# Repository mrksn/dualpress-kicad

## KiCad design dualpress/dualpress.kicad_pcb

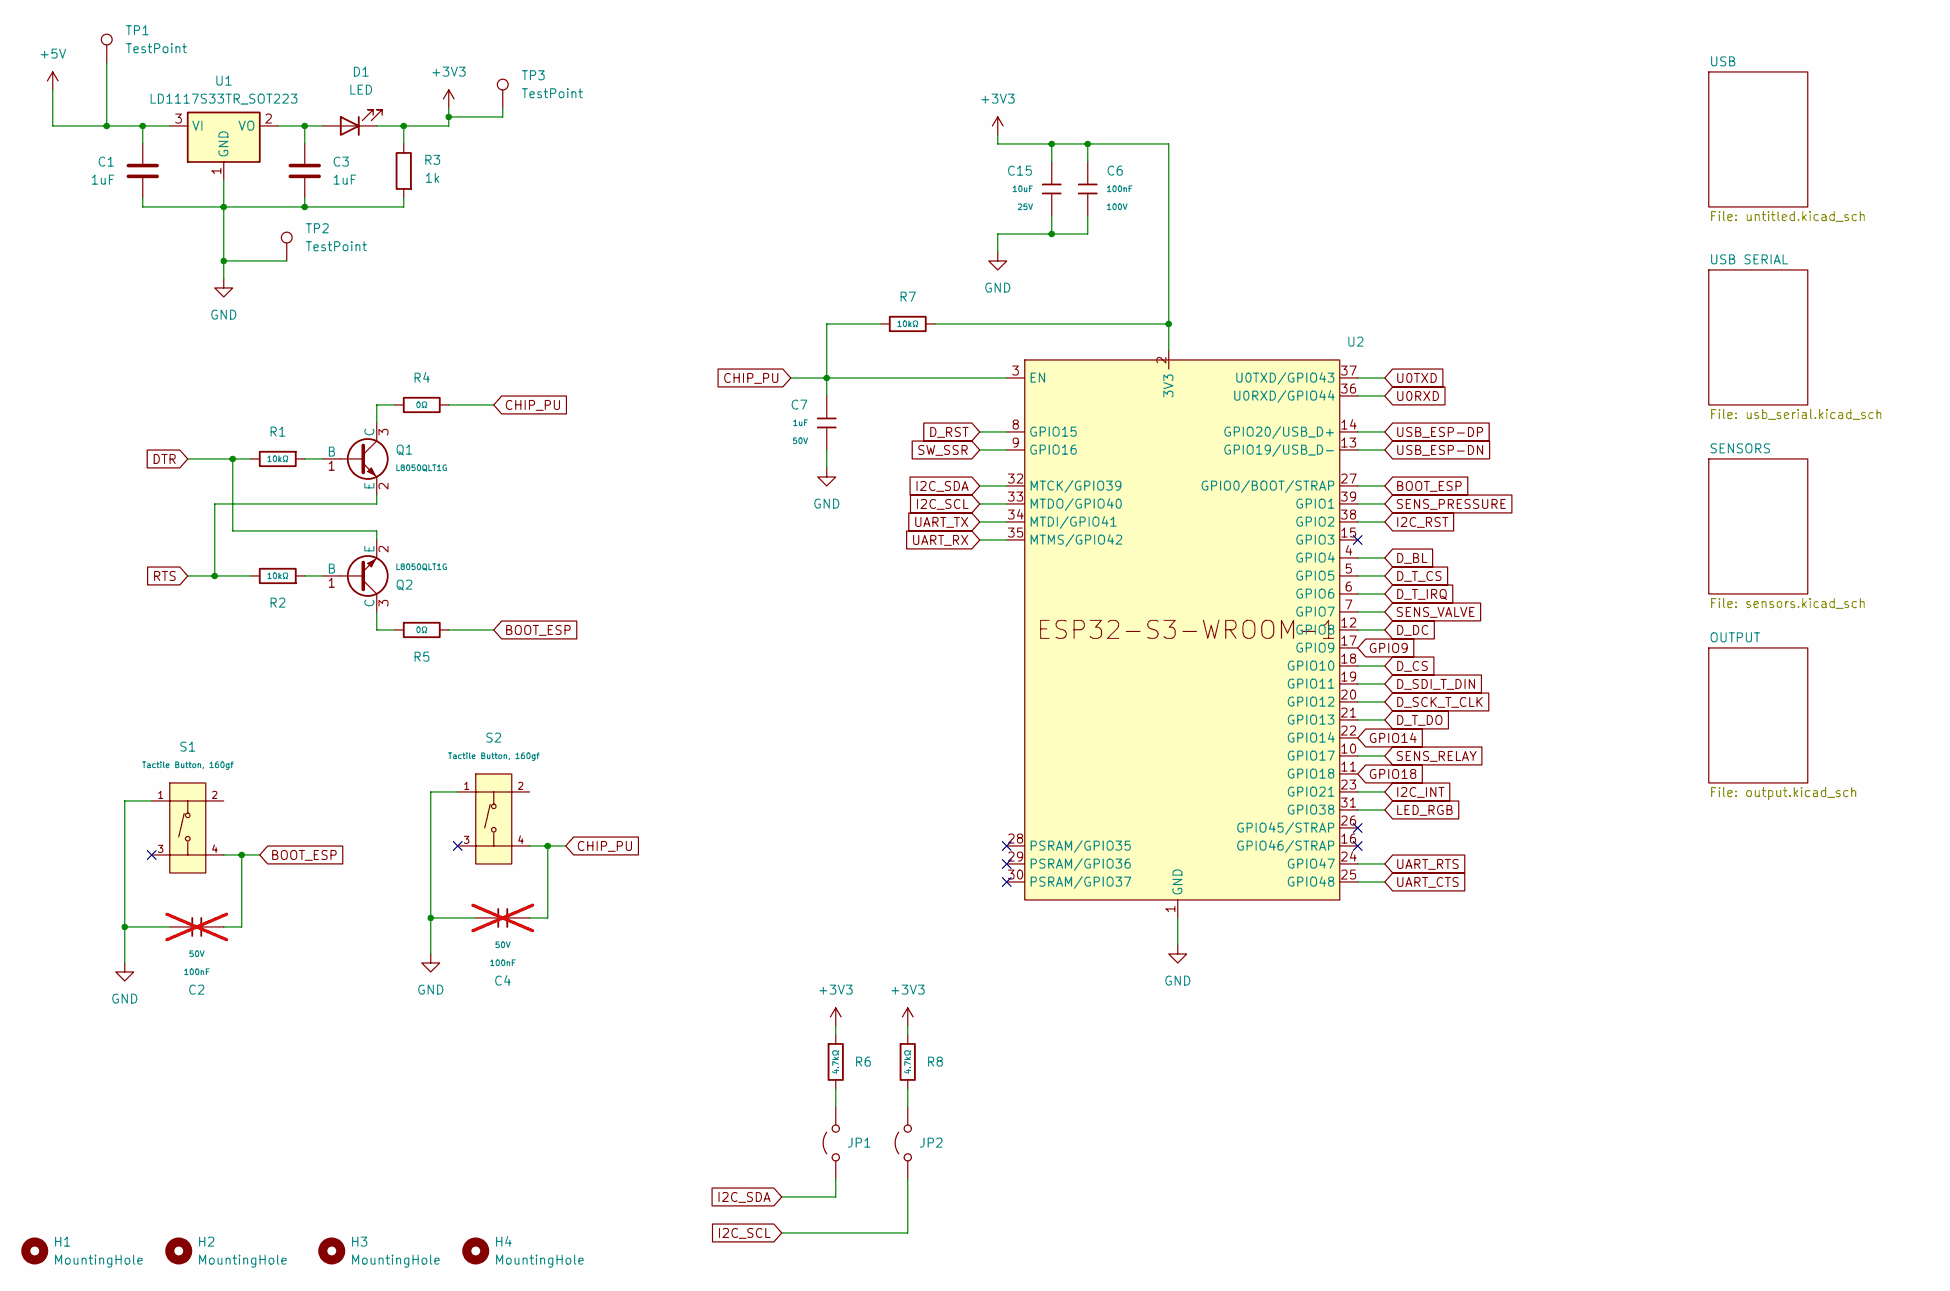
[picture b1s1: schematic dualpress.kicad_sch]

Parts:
C1, C3: 1uF; C_0805; JLCPCB C28323
C2, C4: 100nF; C_0805; Voltage Rated 50V; Tolerance ±10%; Part CC0603KRX7R9BB104; LCSC C14663; not fitted
C6: 100nF; C_0805; Voltage Rated 100V; Tolerance ±10%; Part CL21B104KCFNNNE; LCSC C28233
C7: 1uF; C_0805; Voltage Rated 50V; Tolerance ±10%; Part CL21B105KBFNNNE; LCSC C28323
C15: 10uF; C_0805; Voltage Rated 25V; Tolerance ±10%; Part CL21A106KAYNNNE; LCSC C15850
D1: LED; D_0603; JLCPCB C2286
H1, H2, H3, H4: MountingHole; MountingHole_3.2mm_M3
JP1, JP2: Jumper_2_Open; PinHeader_1x02_P2.54mm_Vertical
Q1: L8050QLT1G; Q_SOT-23; Part L8050QLT1G; LCSC C49581
Q2: L8050QLT1G; Q_SOT-23; Part SS8050; LCSC C7420370
R1, R2, R7: 10kΩ; R_0603; Overload Voltage (Max) 75V; Tolerance ±1%; Part 0603WAF1002T5E; LCSC C25804
R3: 1k; R_0603; JLCPCB C22548
R4, R5: 0Ω; R_0603; Overload Voltage (Max) 75V; Tolerance ±1%; Part 0603WAF0000T5E; LCSC C21189
R6, R8: 4.7kΩ; R_0603; Overload Voltage (Max) 75V; Tolerance ±1%; Part 0603WAF4701T5E; LCSC C23162
S1: Tactile Button, 160gf; Voltage Rating (Dc) 12V; Part TS-1088-AR02016; LCSC C720477
S2: Tactile Button, 160gf; Voltage Rating (Dc) 12V; Part TS-1187A-B-A-B; LCSC C318884
TP1, TP2, TP3: TestPoint; TestPoint_Pad_D1.5mm
U1: LD1117S33TR_SOT223; SOT-223-3_TabPin2; JLCPCB C86781
U2: ESP32-S3-WROOM-1; JLCPCB C2913202

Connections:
+3V3: C6.1, C15.1, D1.1 (K), R3.1, R6.1, R7.2, R8.1, TP3.1 (1_1), U2.2 (3V3); also elsewhere on the board
+5V: C1.2, TP1.1 (1_1), U1.3 (VI); also elsewhere on the board
BOOT_ESP: C2.1, R5.2, S1.4 (D), U2.27 (GPIO0/BOOT/STRAP)
CHIP_PU: C4.1, C7.1, R4.2, R7.1, S2.4 (D), U2.3 (EN)
DTR: Q2.2 (E), R1.2; also elsewhere on the board
D_BL: U2.4 (GPIO4); also elsewhere on the board
D_CS: U2.18 (GPIO10); also elsewhere on the board
D_DC: U2.12 (GPIO8); also elsewhere on the board
D_RST: U2.8 (GPIO15); also elsewhere on the board
D_SCK_T_CLK: U2.20 (GPIO12); also elsewhere on the board
D_SDI_T_DIN: U2.19 (GPIO11); also elsewhere on the board
D_T_CS: U2.5 (GPIO5); also elsewhere on the board
D_T_DO: U2.21 (GPIO13); also elsewhere on the board
D_T_IRQ: U2.6 (GPIO6); also elsewhere on the board
GND: C1.1, C2.2, C3.2, C4.2, C6.2, C7.2, C15.2, R3.2, S1.1 (A), S2.1 (A), TP2.1 (1_1), U1.1 (GND), U2.1 (GND); also elsewhere on the board
GPIO9: U2.17 (GPIO9); also elsewhere on the board
GPIO14: U2.22 (GPIO14); also elsewhere on the board
GPIO18: U2.11 (GPIO18); also elsewhere on the board
I2C_INT: U2.23 (GPIO21); also elsewhere on the board
I2C_RST: U2.38 (GPIO2); also elsewhere on the board
I2C_SCL: JP2.1 (A), U2.33 (MTDO/GPIO40); also elsewhere on the board
I2C_SDA: JP1.1 (A), U2.32 (MTCK/GPIO39); also elsewhere on the board
LED_RGB: U2.31 (GPIO38); also elsewhere on the board
unnamed: C3.1, D1.2 (A), U1.2 (VO)
unnamed: JP1.2 (B), R6.2
unnamed: JP2.2 (B), R8.2
unnamed: Q1.1 (B), R1.1
unnamed: Q1.3 (C), R4.1
unnamed: Q2.1 (B), R2.1
unnamed: Q2.3 (C), R5.1
unnamed: U2.40 (GND), U2.41 (GND)
RTS: Q1.2 (E), R2.2; also elsewhere on the board
SENS_PRESSURE: U2.39 (GPIO1); also elsewhere on the board
SENS_RELAY: U2.10 (GPIO17); also elsewhere on the board
SENS_VALVE: U2.7 (GPIO7); also elsewhere on the board
SW_SSR: U2.9 (GPIO16); also elsewhere on the board
U0RXD: U2.36 (U0RXD/GPIO44); also elsewhere on the board
U0TXD: U2.37 (U0TXD/GPIO43); also elsewhere on the board
UART_CTS: U2.25 (GPIO48); also elsewhere on the board
UART_RTS: U2.24 (GPIO47); also elsewhere on the board
UART_RX: U2.35 (MTMS/GPIO42); also elsewhere on the board
UART_TX: U2.34 (MTDI/GPIO41); also elsewhere on the board
USB_ESP-DN: U2.13 (GPIO19/USB_D-); also elsewhere on the board
USB_ESP-DP: U2.14 (GPIO20/USB_D+); also elsewhere on the board

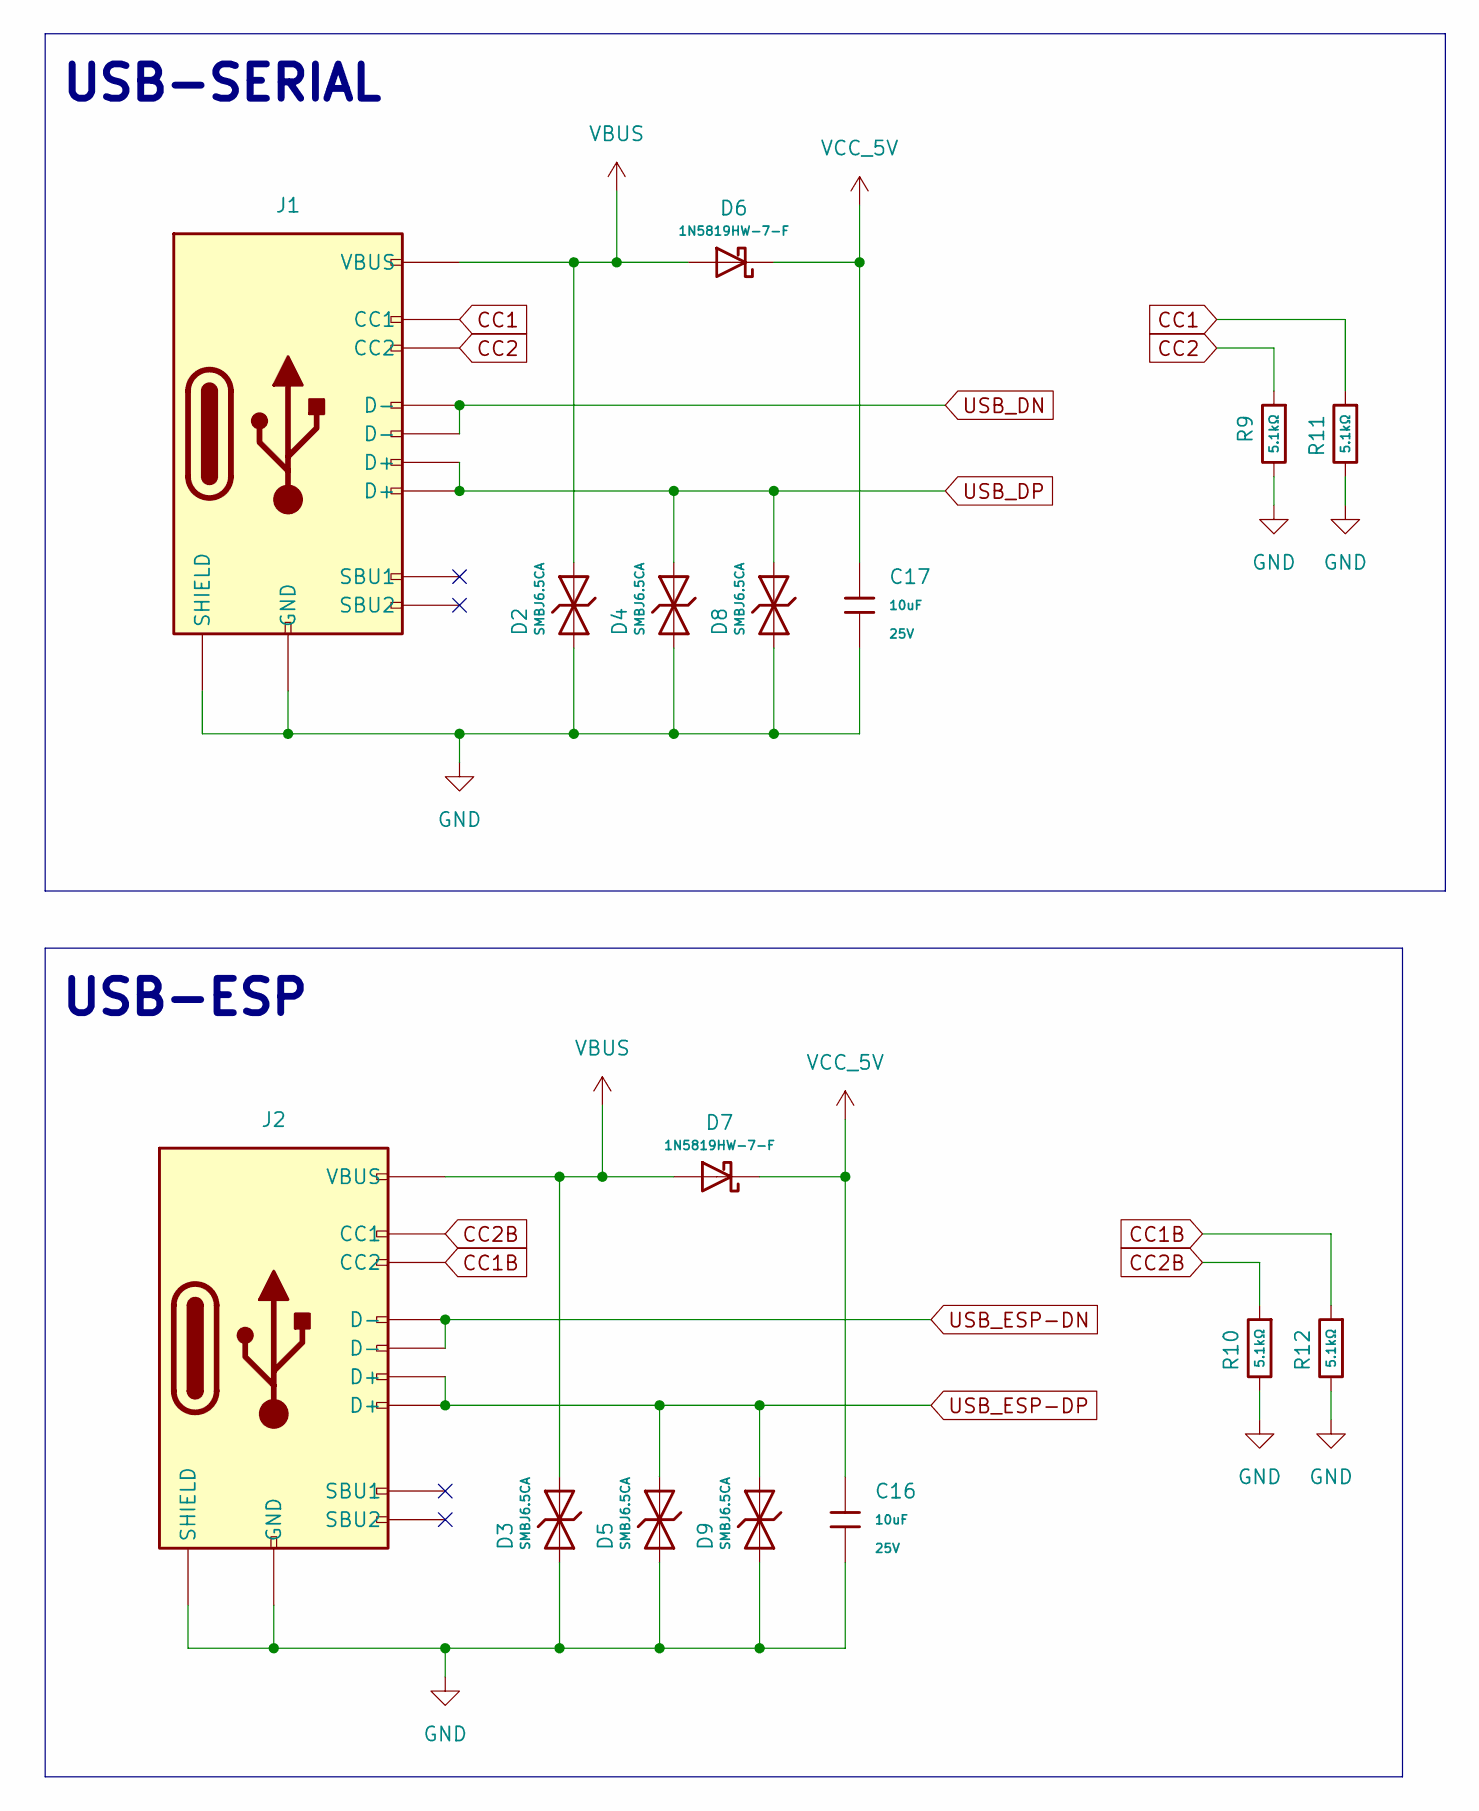
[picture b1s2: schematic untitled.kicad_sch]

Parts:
C16, C17: 10uF; C_0805; Voltage Rated 25V; Tolerance ±10%; Part CL21A106KAYNNNE; LCSC C15850
D2, D3, D4, D5, D8, D9: SMBJ6.5CA; D_SMB; Breakdown Voltage 7.22V; Part SMBJ6.5CA; LCSC C7420377
D6: 1N5819HW-7-F; D_SOD-123; Forward Voltage (Vf@If) 600mV@1A; Reverse Voltage (Vr) 40V; Part 1N5819HW-7-F; LCSC C82544
D7: 1N5819HW-7-F; D_SOD-123; Forward Voltage (Vf@If) 600mV@1A; Reverse Voltage (Vr) 40V; Part 1N5819WS; LCSC C191023
J1, J2: Connector, USB-TYPE-C-16P; TYPE-C-SMD_HX-TYPE-C-16PIN; LCSC C2927039
R9, R10, R11, R12: 5.1kΩ; R_0603; Overload Voltage (Max) 75V; Tolerance ±1%; Part 0603WAF5101T5E; LCSC C23186

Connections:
CC1: J1.A5 (CC1), R11.1
CC1B: J2.B5 (CC2), R12.1
CC2: J1.B5 (CC2), R9.1
CC2B: J2.A5 (CC1), R10.1
GND: C16.2, C17.2, D2.1, D3.1, D4.1, D5.1, D8.1, D9.1, J1.A12B1 (GND), J1.B12A1 (GND), J1.S1 (SHIELD), J2.A12B1 (GND), J2.B12A1 (GND), J2.S1 (SHIELD), R9.2, R10.2, R11.2, R12.2; also elsewhere on the board
USB_DN: J1.A7 (D-), J1.B7 (D-); also elsewhere on the board
USB_DP: D4.2, D8.2, J1.A6 (D+), J1.B6 (D+); also elsewhere on the board
USB_ESP-DN: J2.A7 (D-), J2.B7 (D-); also elsewhere on the board
USB_ESP-DP: D5.2, D9.2, J2.A6 (D+), J2.B6 (D+); also elsewhere on the board
VBUS: D2.2, D3.2, D6.2, D7.2, J1.A9B4 (VBUS), J1.B9A4 (VBUS), J2.A9B4 (VBUS), J2.B9A4 (VBUS); also elsewhere on the board
VCC_5V: C16.1, C17.1, D6.1, D7.1

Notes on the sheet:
USB-ESP
USB-SERIAL

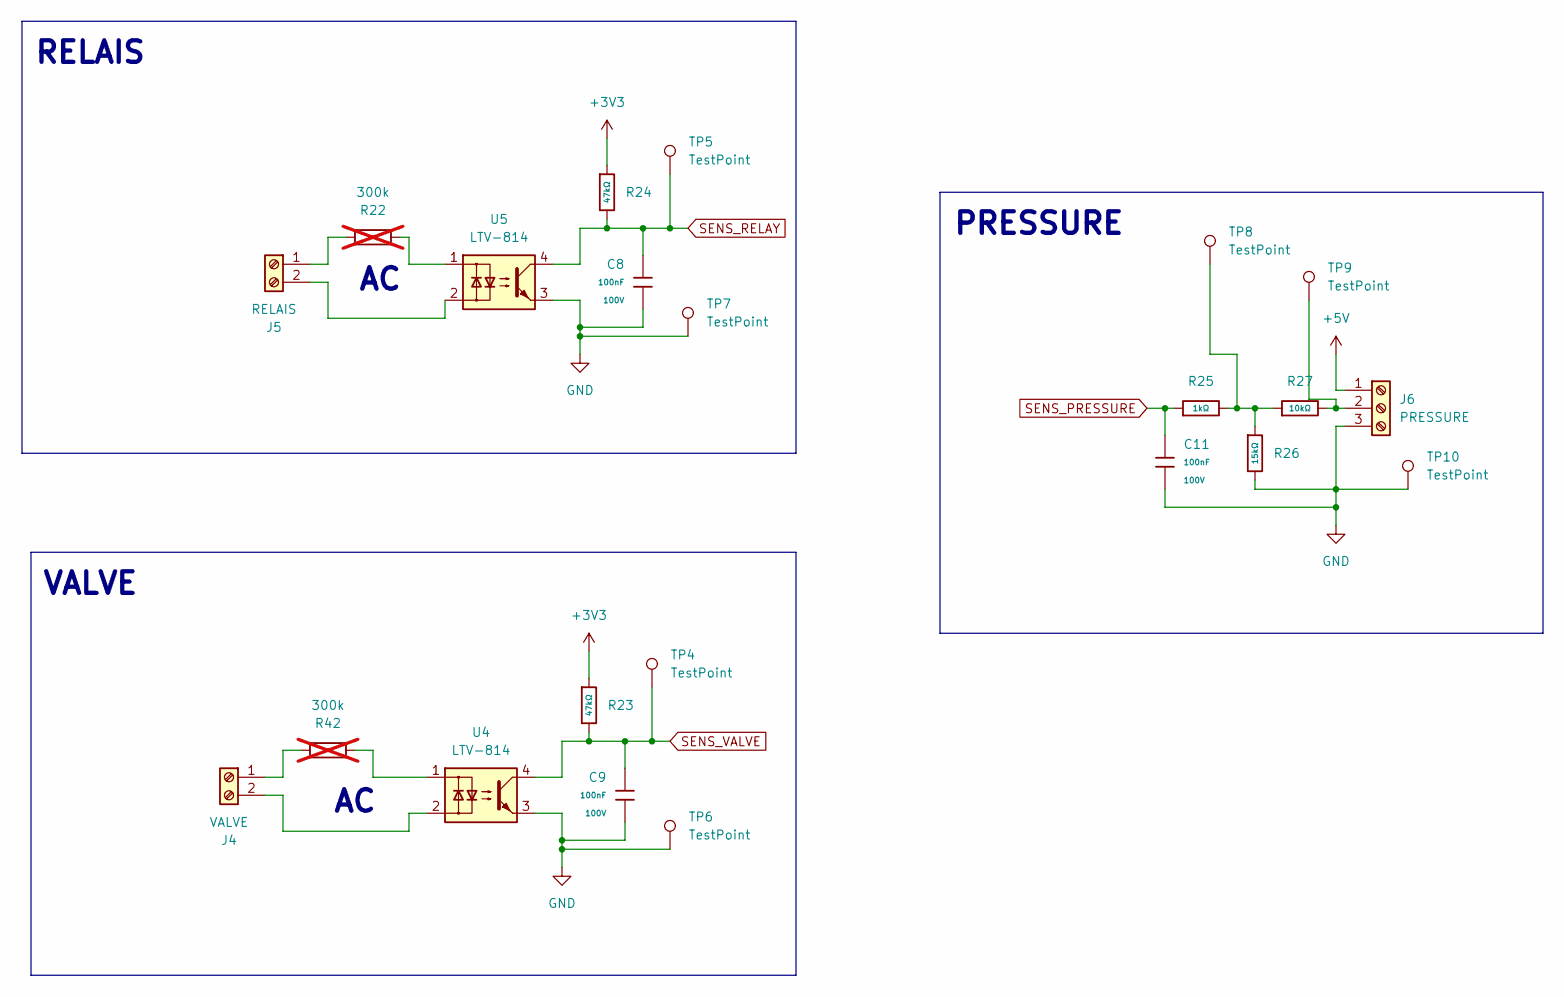
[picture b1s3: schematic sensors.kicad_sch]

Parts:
C8, C9, C11: 100nF; C_0805; Voltage Rated 100V; Tolerance ±10%; Part CL21B104KCFNNNE; LCSC C28233
J4: VALVE; TerminalBlock_MaiXu_MX126-5.0-02P_1x02_P5.00mm
J5: RELAIS; TerminalBlock_MaiXu_MX126-5.0-02P_1x02_P5.00mm
J6: PRESSURE; TerminalBlock_MaiXu_MX126-5.0-03P_1x03_P5.00mm
R22, R42: 300k; CP_Axial_L11.0mm_D5.0mm_P18.00mm_Horizontal; JLCPCB C601006; not fitted
R23, R24: 47kΩ; R_0603; Overload Voltage (Max) 75V; Tolerance ±1%; Part 0603WAF4702T5E; LCSC C25819
R25: 1kΩ; R_0603; Overload Voltage (Max) 75V; Tolerance ±1%; Part 0603WAF1001T5E; LCSC C21190
R26: 15kΩ; R_0603; Overload Voltage (Max) 75V; Tolerance ±1%; Part 0603WAF1502T5E; LCSC C22809
R27: 10kΩ; R_0603; Overload Voltage (Max) 75V; Tolerance ±1%; Part 0603WAF1002T5E; LCSC C25804
TP4, TP5, TP6, TP7, TP8, TP9, TP10: TestPoint; TestPoint_Pad_D1.5mm
U4, U5: LTV-814; DIP-4_W7.62mm; JLC C125118

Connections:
+3V3: R23.1, R24.1; also elsewhere on the board
+5V: J6.1; also elsewhere on the board
GND: C8.2, C9.2, C11.2, J6.3, R26.2, TP6.1 (1_1), TP7.1 (1_1), TP10.1 (1_1), U4.3, U5.3; also elsewhere on the board
unnamed: J4.1, R42.2
unnamed: J4.2, U4.2
unnamed: J5.1, R22.2
unnamed: J5.2, U5.2
unnamed: J6.2, R27.2, TP9.1 (1_1)
unnamed: R22.1, U5.1
unnamed: R25.2, R26.1, R27.1, TP8.1 (1_1)
unnamed: R42.1, U4.1
SENS_PRESSURE: C11.1, R25.1; also elsewhere on the board
SENS_RELAY: C8.1, R24.2, TP5.1 (1_1), U5.4; also elsewhere on the board
SENS_VALVE: C9.1, R23.2, TP4.1 (1_1), U4.4; also elsewhere on the board

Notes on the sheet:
PRESSURE
VALVE
RELAIS

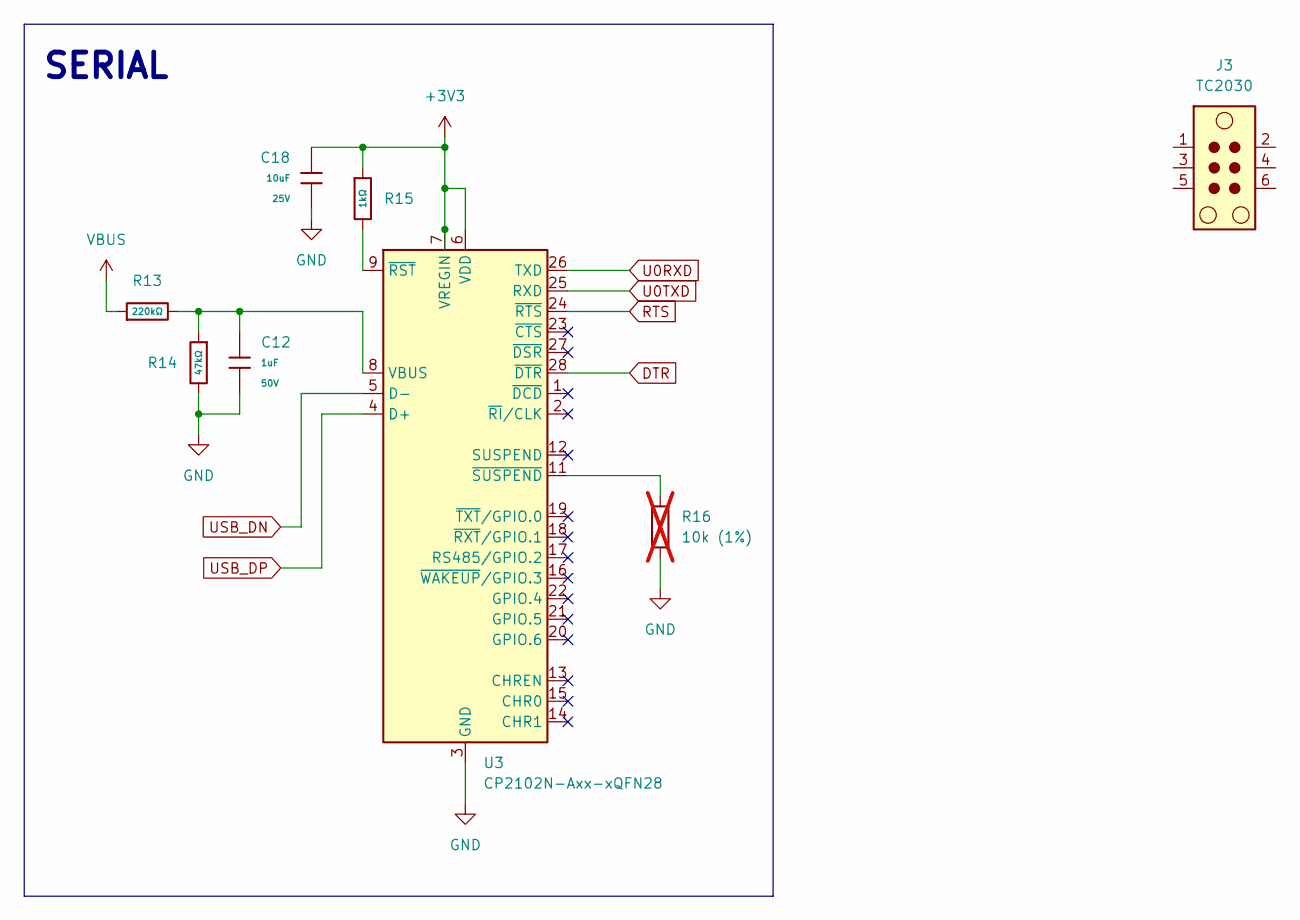
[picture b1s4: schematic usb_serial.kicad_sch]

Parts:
C12: 1uF; C_0805; Voltage Rated 50V; Tolerance ±10%; Part CL21B105KBFNNNE; LCSC C28323
C18: 10uF; C_0805; Voltage Rated 25V; Tolerance ±10%; Part CL21A106KAYNNNE; LCSC C15850
J3: TC2030; Tag-Connect_TC2030-IDC-NL_2x03_P1.27mm_Vertical
R13: 220kΩ; R_0603; Overload Voltage (Max) 75V; Tolerance ±1%; Part 0603WAF2203T5E; LCSC C22961
R14: 47kΩ; R_0603; Overload Voltage (Max) 75V; Tolerance ±1%; Part 0603WAF4702T5E; LCSC C25819
R15: 1kΩ; R_0603; Overload Voltage (Max) 75V; Tolerance ±1%; Part 0603WAF1001T5E; LCSC C21190
R16: 10k (1%); R_0603; JLCPCB C116677; not fitted
U3: CP2102N-Axx-xQFN28; QFN-28-1EP_5x5mm_P0.5mm_EP3.35x3.35mm; JLCPCB C964632

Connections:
+3V3: C18.1, R15.1, U3.6 (VDD), U3.7 (VREGIN); also elsewhere on the board
DTR: U3.28 (~DTR); also elsewhere on the board
GND: C12.2, C18.2, R14.2, R16.2, U3.3 (GND), U3.29 (GND); also elsewhere on the board
unnamed: C12.1, R13.2, R14.1, U3.8 (VBUS)
unnamed: R15.2, U3.9 (~RST)
unnamed: R16.1, U3.11 (~SUSPEND)
RTS: U3.24 (~RTS); also elsewhere on the board
U0RXD: U3.26 (TXD); also elsewhere on the board
U0TXD: U3.25 (RXD); also elsewhere on the board
USB_DN: U3.5 (D-); also elsewhere on the board
USB_DP: U3.4 (D+); also elsewhere on the board
VBUS: R13.1; also elsewhere on the board

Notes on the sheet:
SERIAL

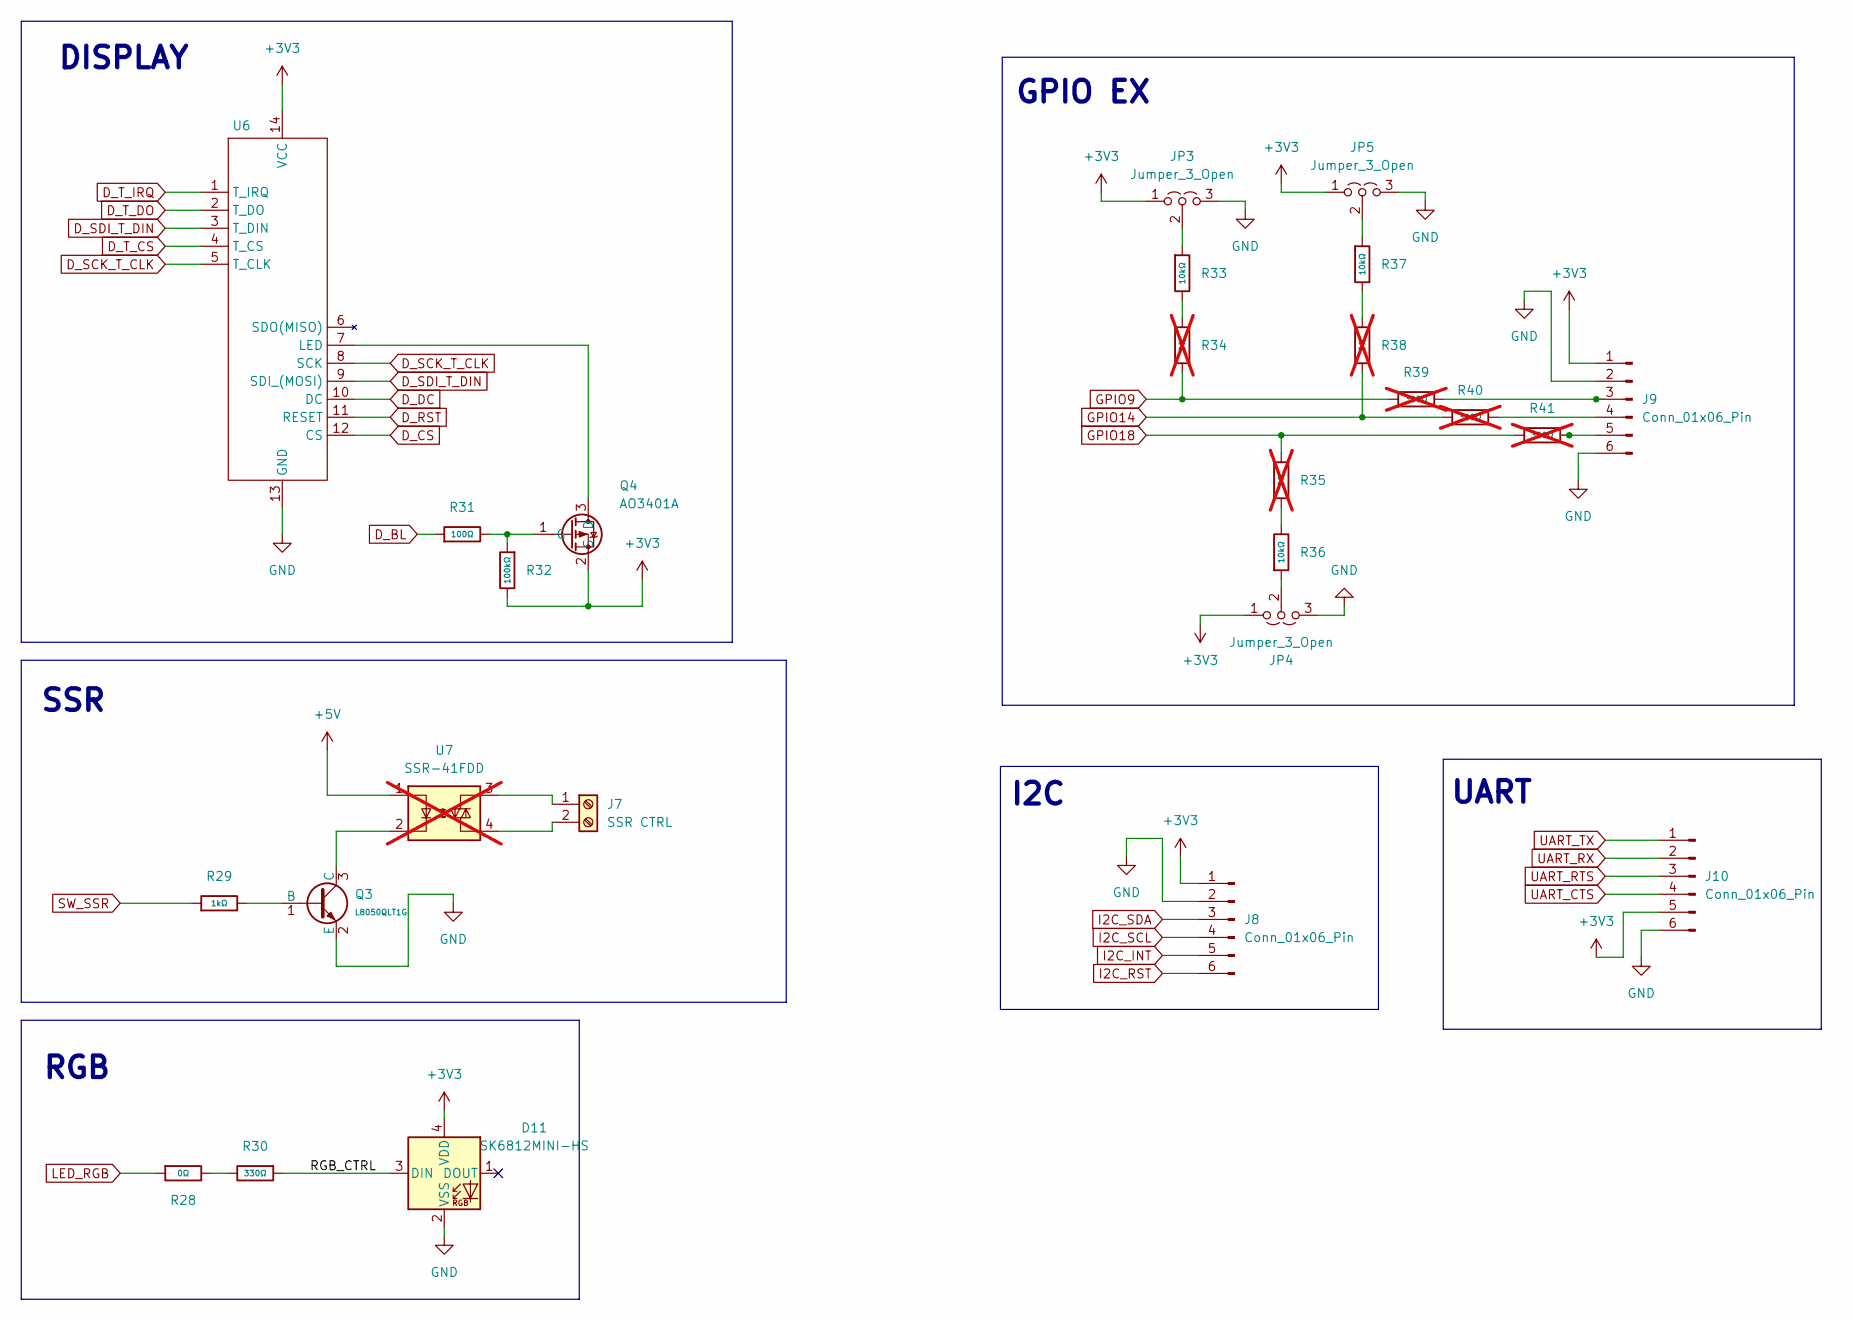
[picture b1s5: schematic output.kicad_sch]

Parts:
D11: SK6812MINI-HS; JLCPCB C2922787
J7: SSR CTRL; TerminalBlock_MaiXu_MX126-5.0-02P_1x02_P5.00mm
J8, J9, J10: Conn_01x06_Pin; JST_XH_B6B-XH-AM_1x06_P2.50mm_Vertical
JP3, JP4, JP5: Jumper_3_Open; PinHeader_1x03_P2.54mm_Vertical
Q3: L8050QLT1G; Q_SOT-23; Part S8050; LCSC C364312
Q4: AO3401A; SOT-23; JLCPCB C15127
R28: 0Ω; R_0603; Overload Voltage (Max) 75V; Tolerance ±1%; Part 0603WAF0000T5E; LCSC C21189
R29: 1kΩ; R_0603; Overload Voltage (Max) 75V; Tolerance ±1%; Part 0603WAF1001T5E; LCSC C21190
R30: 330Ω; R_0603; Overload Voltage (Max) 75V; Tolerance ±1%; Part 0603WAF3300T5E; LCSC C23138
R31: 100Ω; R_0805; Overload Voltage (Max) 150V; Tolerance ±1%; Part 0805W8F1000T5E; LCSC C17408
R32: 100kΩ; R_0603; Overload Voltage (Max) 150V; Tolerance ±1%; Part 0805W8F1003T5E; LCSC C149504
R33, R36, R37: 10kΩ; R_0603; Overload Voltage (Max) 75V; Tolerance ±1%; Part 0603WAF1002T5E; LCSC C25804
R34, R35, R38: 0Ω; R_0603; Overload Voltage (Max) 75V; Tolerance ±1%; Part 0603WAF0000T5E; LCSC C21189; not fitted
R39, R40, R41: 300Ω; R_1206; Overload Voltage (Max) 200V; Tolerance ±1%; Part 1206W4F3000T5E; LCSC C17887; not fitted
U6: 2.8" Touch Display SPI 14x1; PinHeader_1x14_P2.54mm_Vertical
U7: SSR-41FDD; not fitted

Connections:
+3V3: D11.4 (VDD), J8.1, J9.1, J10.5, JP3.1 (A), JP4.1 (A), JP5.1 (A), Q4.2 (S), R32.2, U6.14 (VCC); also elsewhere on the board
+5V: U7.1; also elsewhere on the board
/OUTPUT/RGB_CTRL: D11.3 (DIN), R30.1
D_BL: R31.1; also elsewhere on the board
D_CS: U6.12 (CS); also elsewhere on the board
D_DC: U6.10 (DC); also elsewhere on the board
D_RST: U6.11 (RESET); also elsewhere on the board
D_SCK_T_CLK: U6.5 (T_CLK), U6.8 (SCK); also elsewhere on the board
D_SDI_T_DIN: U6.3 (T_DIN), U6.9 (SDI_(MOSI)); also elsewhere on the board
D_T_CS: U6.4 (T_CS); also elsewhere on the board
D_T_DO: U6.2 (T_DO); also elsewhere on the board
D_T_IRQ: U6.1 (T_IRQ); also elsewhere on the board
GND: D11.2 (VSS), J8.2, J9.2, J9.6, J10.6, JP3.3 (B), JP4.3 (B), JP5.3 (B), Q3.2 (E), U6.13 (GND); also elsewhere on the board
GPIO9: R34.2, R39.1; also elsewhere on the board
GPIO14: R38.2, R40.1; also elsewhere on the board
GPIO18: R35.1, R41.1; also elsewhere on the board
I2C_INT: J8.5; also elsewhere on the board
I2C_RST: J8.6; also elsewhere on the board
I2C_SCL: J8.4; also elsewhere on the board
I2C_SDA: J8.3; also elsewhere on the board
LED_RGB: R28.1; also elsewhere on the board
unnamed: J7.1, U7.3
unnamed: J7.2, U7.4
unnamed: J9.3, R39.2
unnamed: J9.4, R40.2
unnamed: J9.5, R41.2
unnamed: JP3.2 (C), R33.1
unnamed: JP4.2 (C), R36.1
unnamed: JP5.2 (C), R37.1
unnamed: Q3.1 (B), R29.2
unnamed: Q3.3 (C), U7.2
unnamed: Q4.3 (D), U6.7 (LED)
unnamed: Q4.1 (G), R31.2, R32.1
unnamed: R28.2, R30.2
unnamed: R33.2, R34.1
unnamed: R35.2, R36.2
unnamed: R37.2, R38.1
SW_SSR: R29.1; also elsewhere on the board
UART_CTS: J10.4; also elsewhere on the board
UART_RTS: J10.3; also elsewhere on the board
UART_RX: J10.2; also elsewhere on the board
UART_TX: J10.1; also elsewhere on the board

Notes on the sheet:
RGB
GPIO EX
SSR
I2C
DISPLAY
UART

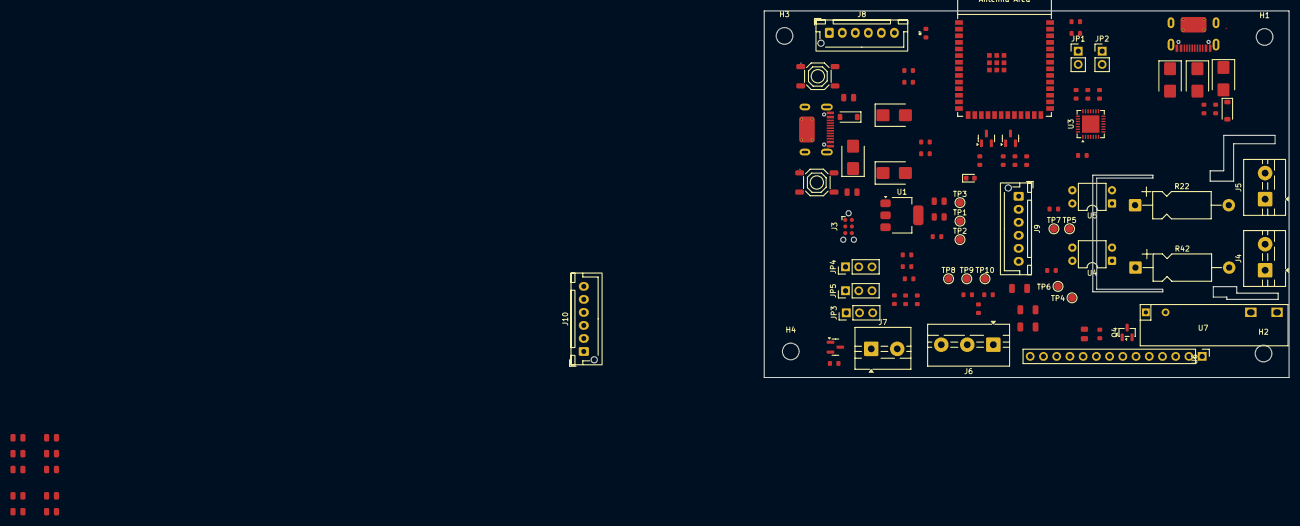
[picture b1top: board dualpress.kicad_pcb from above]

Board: 4 copper layers, 100.8 x 70.4 mm, 102 parts (0 on the bottom side), 79 nets.

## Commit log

2026-06-15 schematic done. footprints need checking
2026-06-15 base layout done
2026-06-16 schematic done
2026-06-18 before remove footprints
2026-06-18 new footprints complete
